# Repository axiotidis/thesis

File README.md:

# "Εφαρμογή απεικόνισης της κατανάλωσης και της ποιότητας του πόσιμου νερού με τη χρήση ασύρματου δικτύου αισθητήρων".

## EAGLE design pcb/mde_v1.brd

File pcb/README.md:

Στο φάκελο αυτό βρίσκεται το αρχείο του τυπωμένου κυκλώματος (PCB)

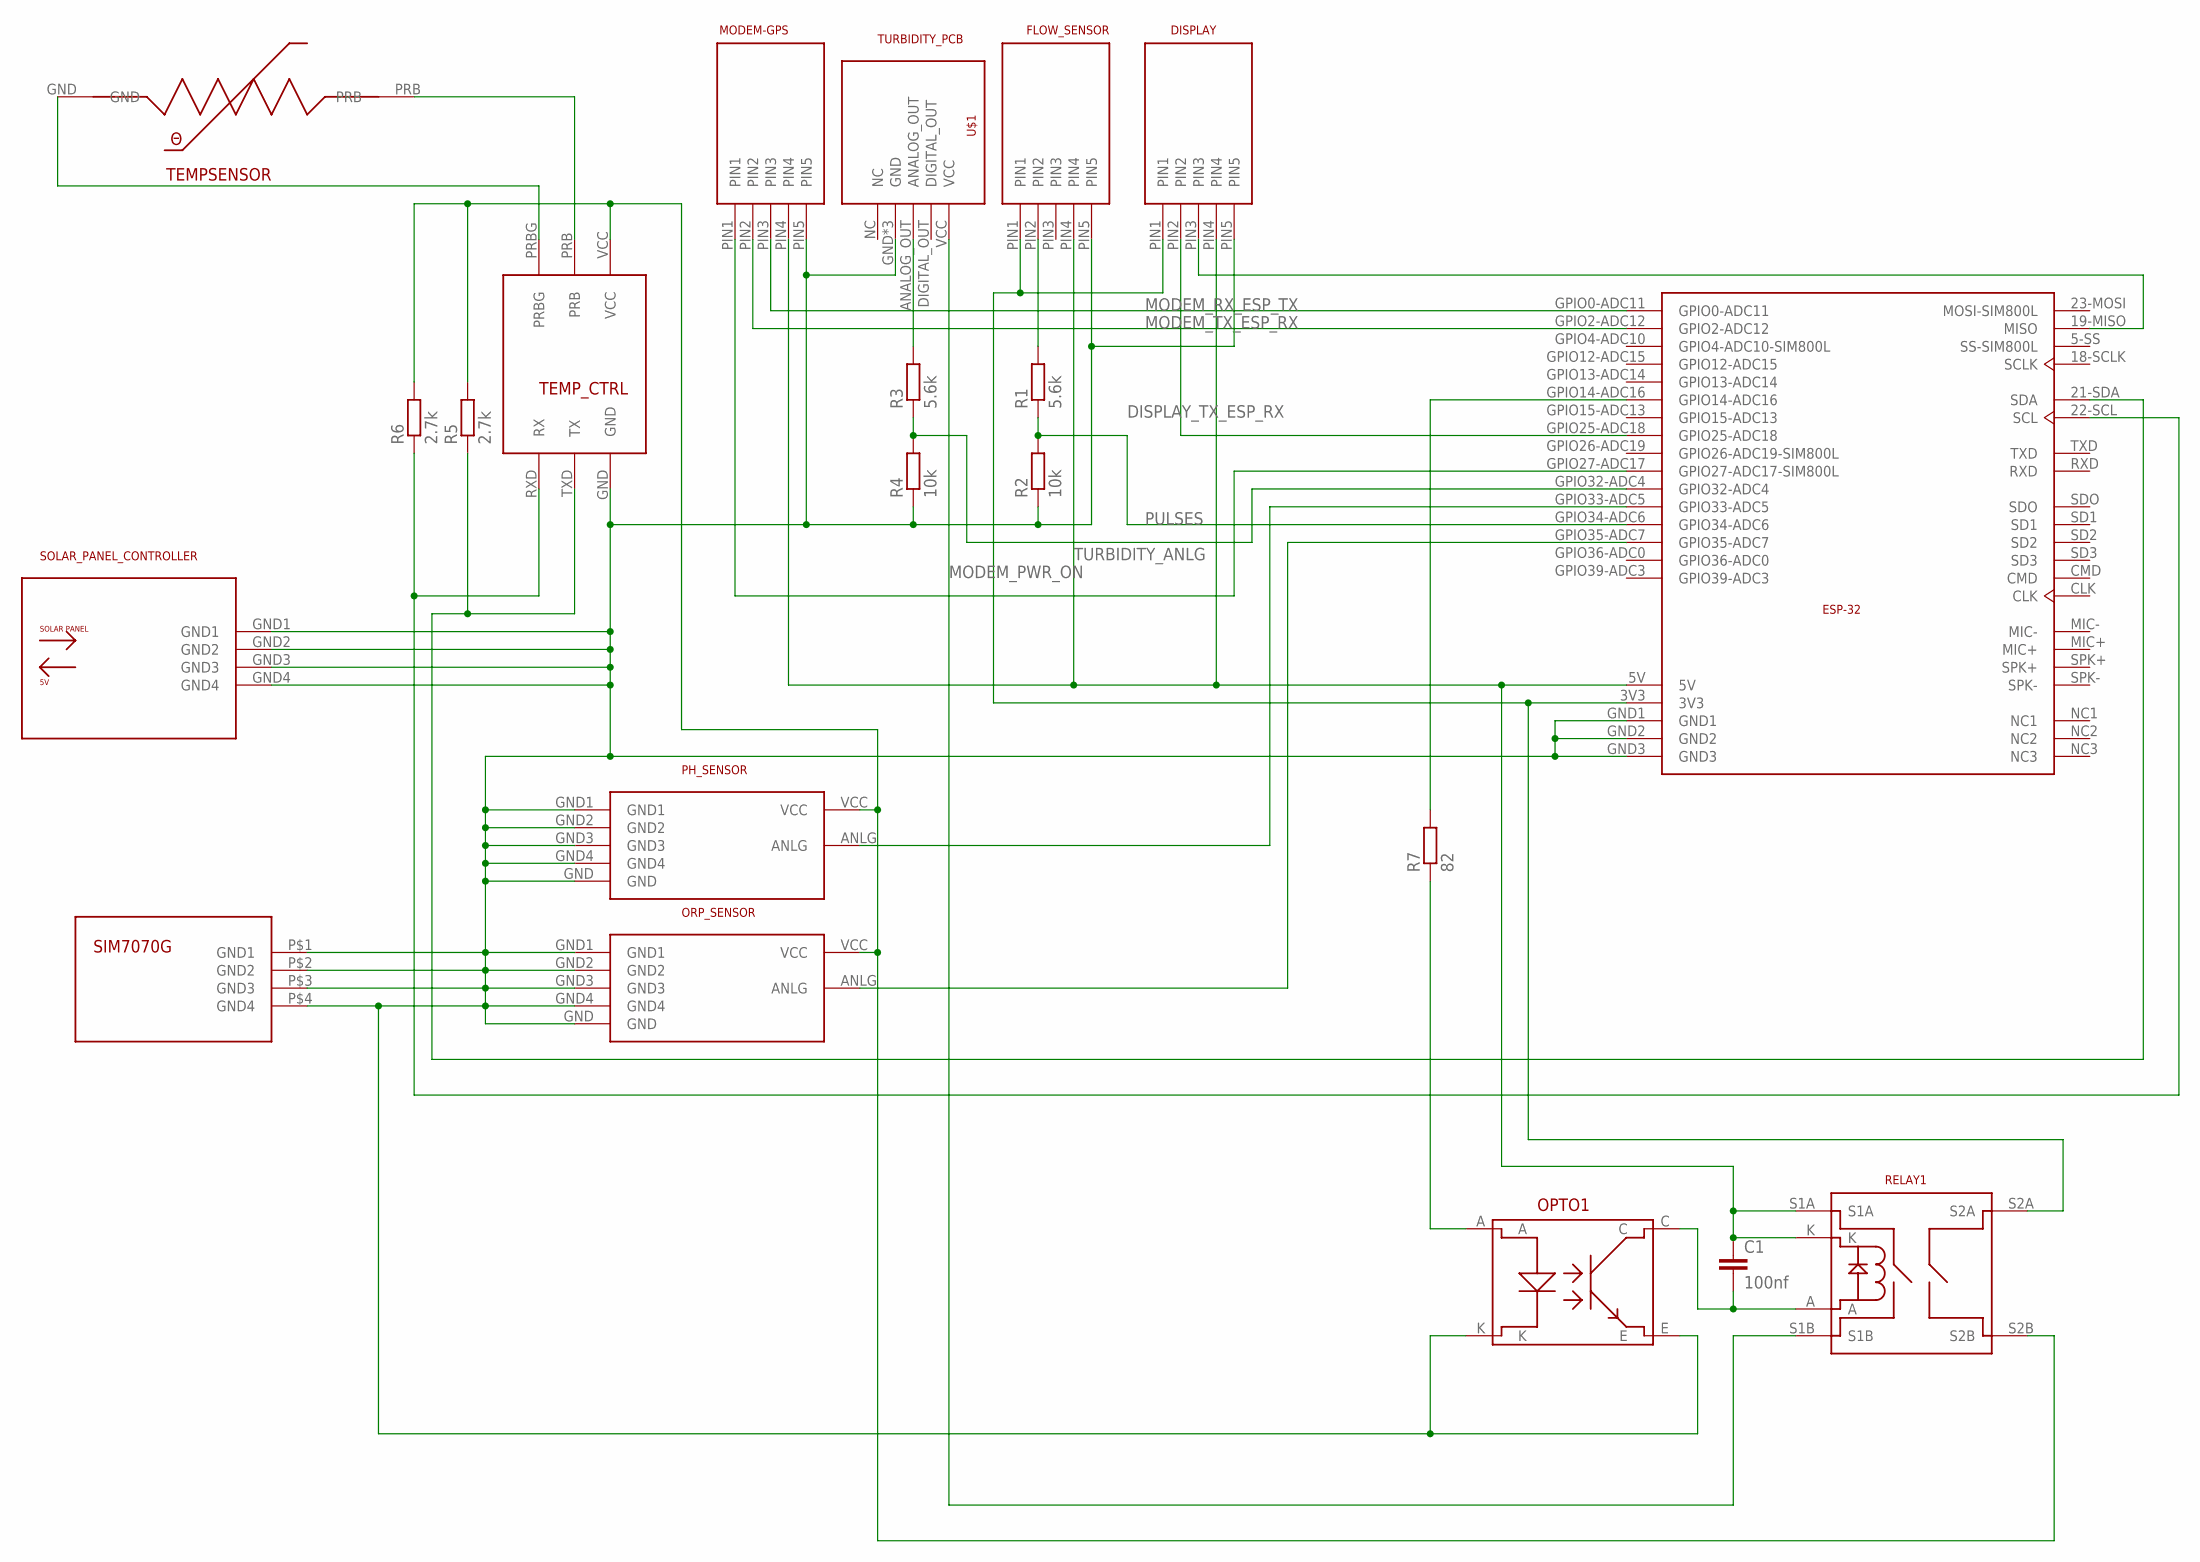
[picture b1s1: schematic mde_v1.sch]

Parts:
C1: 100nf; C2.5-3
DISPLAY: CONNECTOR-JSTXH-5
ESP-32: ESP32-TTGO-SIM800L
FLOW_SENSOR: CONNECTOR-JSTXH-5
MODEM-GPS: CONNECTOR-JSTXH-5
OPTO1: K817P
ORP_SENSOR: GRAVITY-PCB
PH_SENSOR: GRAVITY-PCB
R1, R3: 5.6k; 0207/10
R2, R4: 10k; 0207/10
R5, R6: 2.7k; 0207/10
R7: 82; 0207/10
RELAY1: DIP05-2A72-21D
SIM7070G: SIM7070G
SOLAR_PANEL_CONTROLLER: DFR0559
TEMPSENSOR: TEMP-PROBE
TEMP_CTRL: EZO-RTD
U$1: TURBIDITY_PCB

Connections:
3V3: DISPLAY.PIN1, ESP-32.3V3, FLOW_SENSOR.PIN1, RELAY1.S2A
3V3_SENSORS: ORP_SENSOR.VCC, PH_SENSOR.VCC, R5.2, R6.2, RELAY1.S2B, TEMP_CTRL.VCC
5V: C1.1, DISPLAY.PIN4, ESP-32.5V, FLOW_SENSOR.PIN4, MODEM-GPS.PIN4, RELAY1.K, RELAY1.S1A
5V_SENSOR: RELAY1.S1B, U$1.VCC
DISPLAY_RX_ESP_TX: DISPLAY.PIN3, ESP-32.19-MISO (MISO)
DISPLAY_TX_ESP_RX: DISPLAY.PIN2, ESP-32.GPIO25-ADC18
GND: DISPLAY.PIN5, ESP-32.GND1, ESP-32.GND2, ESP-32.GND3, FLOW_SENSOR.PIN5, MODEM-GPS.PIN5, OPTO1.E, OPTO1.K, ORP_SENSOR.GND, ORP_SENSOR.GND1, ORP_SENSOR.GND2, ORP_SENSOR.GND3, ORP_SENSOR.GND4, PH_SENSOR.GND, PH_SENSOR.GND1, PH_SENSOR.GND2, PH_SENSOR.GND3, PH_SENSOR.GND4, R2.1, R4.1, SIM7070G.P$1 (GND1), SIM7070G.P$2 (GND2), SIM7070G.P$3 (GND3), SIM7070G.P$4 (GND4), SOLAR_PANEL_CONTROLLER.GND1, SOLAR_PANEL_CONTROLLER.GND2, SOLAR_PANEL_CONTROLLER.GND3, SOLAR_PANEL_CONTROLLER.GND4, TEMP_CTRL.GND, U$1.GND, U$1.P$1 (GND), U$1.P$2 (GND)
MODEM_PWR_ON: ESP-32.GPIO27-ADC17 (GPIO27-ADC17-SIM800L), MODEM-GPS.PIN1
MODEM_RX_ESP_TX: ESP-32.GPIO0-ADC11, MODEM-GPS.PIN3
MODEM_TX_ESP_RX: ESP-32.GPIO2-ADC12, MODEM-GPS.PIN2
unnamed: TEMPSENSOR.GND, TEMP_CTRL.PRBG
unnamed: TEMPSENSOR.PRB, TEMP_CTRL.PRB
unnamed: ESP-32.GPIO14-ADC16, R7.2
unnamed: R3.2, U$1.ANALOG_OUT
unnamed: FLOW_SENSOR.PIN2, R1.2
unnamed: ESP-32.GPIO35-ADC7, ORP_SENSOR.ANLG
unnamed: ESP-32.GPIO33-ADC5, PH_SENSOR.ANLG
unnamed: OPTO1.A, R7.1
unnamed: C1.2, OPTO1.C, RELAY1.A
PULSES: ESP-32.GPIO34-ADC6, R1.1, R2.2
SCL: ESP-32.22-SCL (SCL), R6.1, TEMP_CTRL.RXD (RX)
SDA: ESP-32.21-SDA (SDA), R5.1, TEMP_CTRL.TXD (TX)
TURBIDITY_ANLG: ESP-32.GPIO32-ADC4, R3.1, R4.2

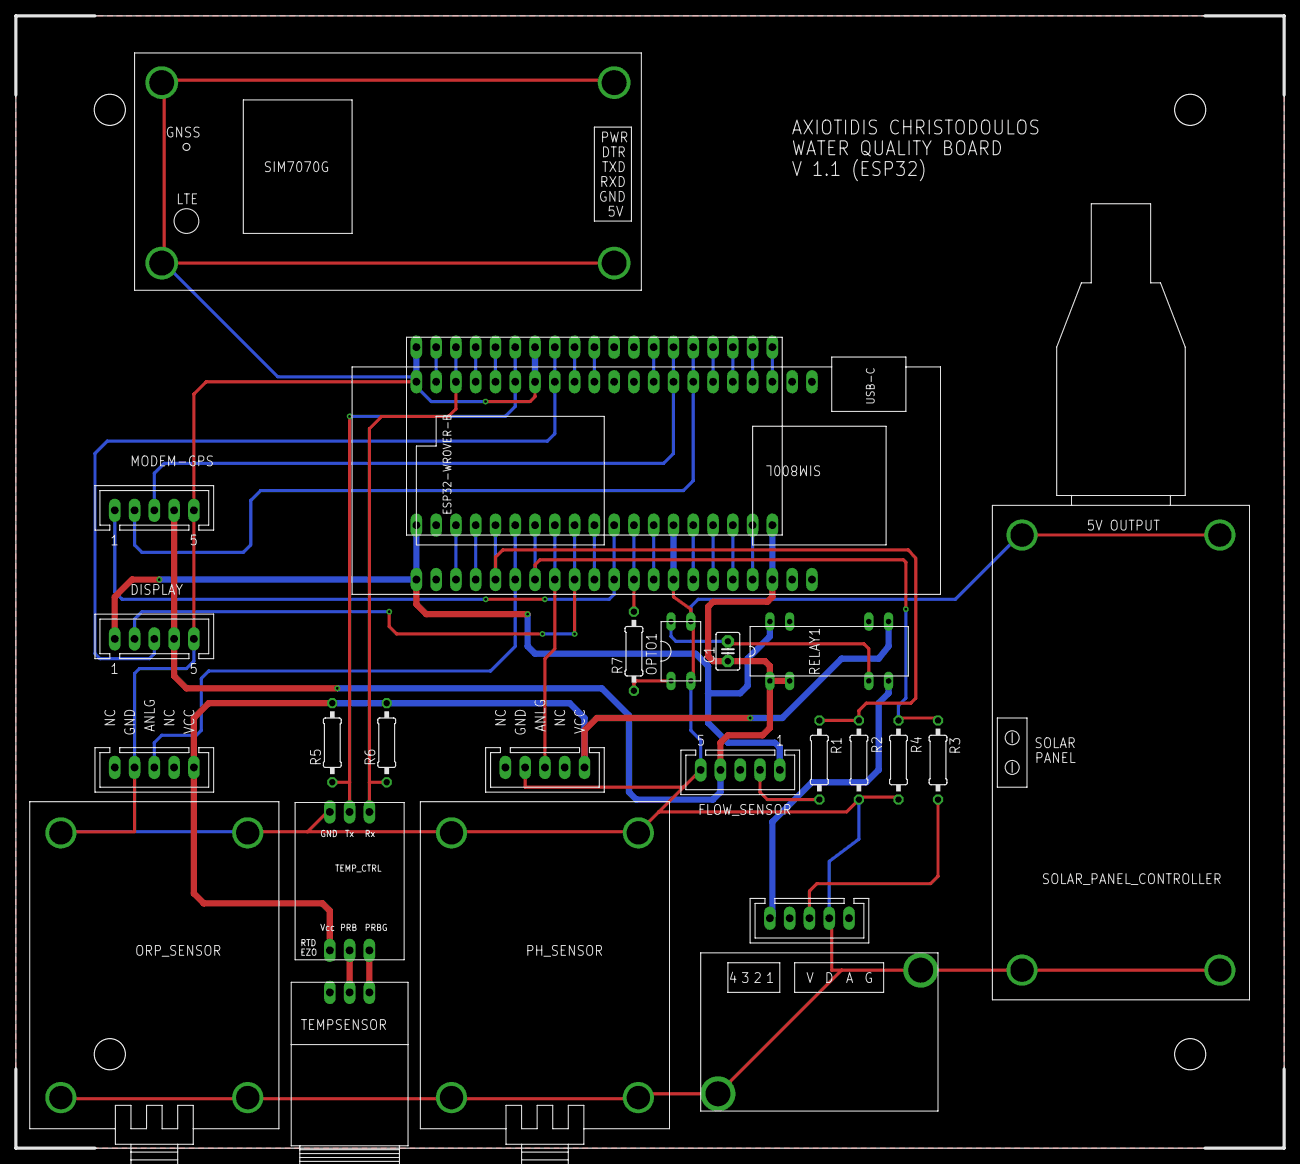
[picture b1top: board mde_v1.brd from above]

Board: 2 copper layers, 162.9 x 145.4 mm, 21 parts (0 on the bottom side), 23 nets.

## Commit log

2021-06-13 Create serviceApp
2021-06-13 Rename androidWebViewApp/AndroidManifest.xml to androidWebViewApp/userApp/AndroidManifest.xml
2021-06-13 Rename androidWebViewApp/MainActivity.java to androidWebViewApp/userApp/MainActivity.java
2021-06-13 Rename androidWebViewApp/activity_main.xml to androidWebViewApp/userApp/activity_main.xml
2021-06-13 Rename androidWebViewApp/AndroidManifest.xml to androidWebViewApp/serviceApp/AndroidManifest.xml
2021-06-13 Rename androidWebViewApp/MainActivity.java to androidWebViewApp/serviceApp/MainActivity.java
2021-06-13 Rename androidWebViewApp/activity_main.xml to androidWebViewApp/serviceApp/activity_main.xml
